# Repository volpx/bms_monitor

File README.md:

# BMS Monitor

Slave BMS module to monitor 24s cells voltages and temperatures.

## Contributors

_Latest first_

- Filippo Volpe

## Features

- 24 cells series
- 32 temperature measurements
- LTC6811-1/-2 both are compatible
- isoSPI cost effective communication interface to the monitor IC directly
- cell balancing
- STM32L0 can be fitted to add logic to the board by itself
- IRda optional communication to the MCU
- compatible, for temperatures, with both NTC and shunt references
- direct SPI connection to the monitor ICs
- usable as two 12S monitor with breakaway slots
- cost reduction in the isolation components if used as 24S monitor
- small footprint, 65mmx115mm

## Configurations

### LTC6811 -1 vs -2

For use with "-1" version the isoSPI link must be daisy chained, hence connecting the master of PORTB to the slave of PORTA of the next IC in the chain. Populate R5 and R6, don't populate R30 R31.

For use with the "-2" version only populate the slave PORTA of each section and connect them in parallel. Then set the address of each section using the solder jumpers. Populate R30 and R31, don't populate R5 R6.

### 24S monitor

Using LTC6811-1 version.

| Component reference         | To fit  | Comment|
|--------------|-----------|------------|
| R11 |   ✔️    |        |
| R12 |   ✔️    |        |
| C18 |   ✔️    |        |
| U12 |   ❌    |        |
| R22 |   ✔️    |        |
| R23 |   ✔️    |        |
| C37 |   ✔️    |        |
| U13 |   ❌    |        |
| FL1 |   ✔️    |        |
| C1 |   ✔️    |        |
| C2 |   ✔️    |        |

### 12S monitor

The board can be splitted along the cutouts to obtain 2 12S monitors of which one has the option to be used with the MCU but both still has full SPI and isoSPI functionality.
In this case using LT6811 -1 or -2 version won't change any functionality.

### Switching PSU

For a more efficient PSU the voltage can be stepped down using a switching regulator.

| Component reference | To fit  | Comment|
|--------------|-----------|------------|
| Q1 |   ❌    |        |

All other PSU components must be populated.

### Low cost PSU

To power the stack monitor a low component count but less efficient psu can be populated using transistor Q1.

| Component reference         | To fit  | Comment|
|--------------|-----------|------------|
| Q1 |   ✔️    |        |
| R14 |   ✔️    |        |
| C19 |   ✔️    |        |
| C21 |   ✔️    |        |
| C27 |   ✔️    |        |
| C29 |   ✔️    |        |

All other PSU components can be left unpopulated.

### SPI vs isoSPI connection

To use the isoSPI connection, connect ISOMD to 1.
To use the direct SPI connection, connect the ISOMD switch to 0 and the ICMP and BIAS resistor can be left unpopulated.

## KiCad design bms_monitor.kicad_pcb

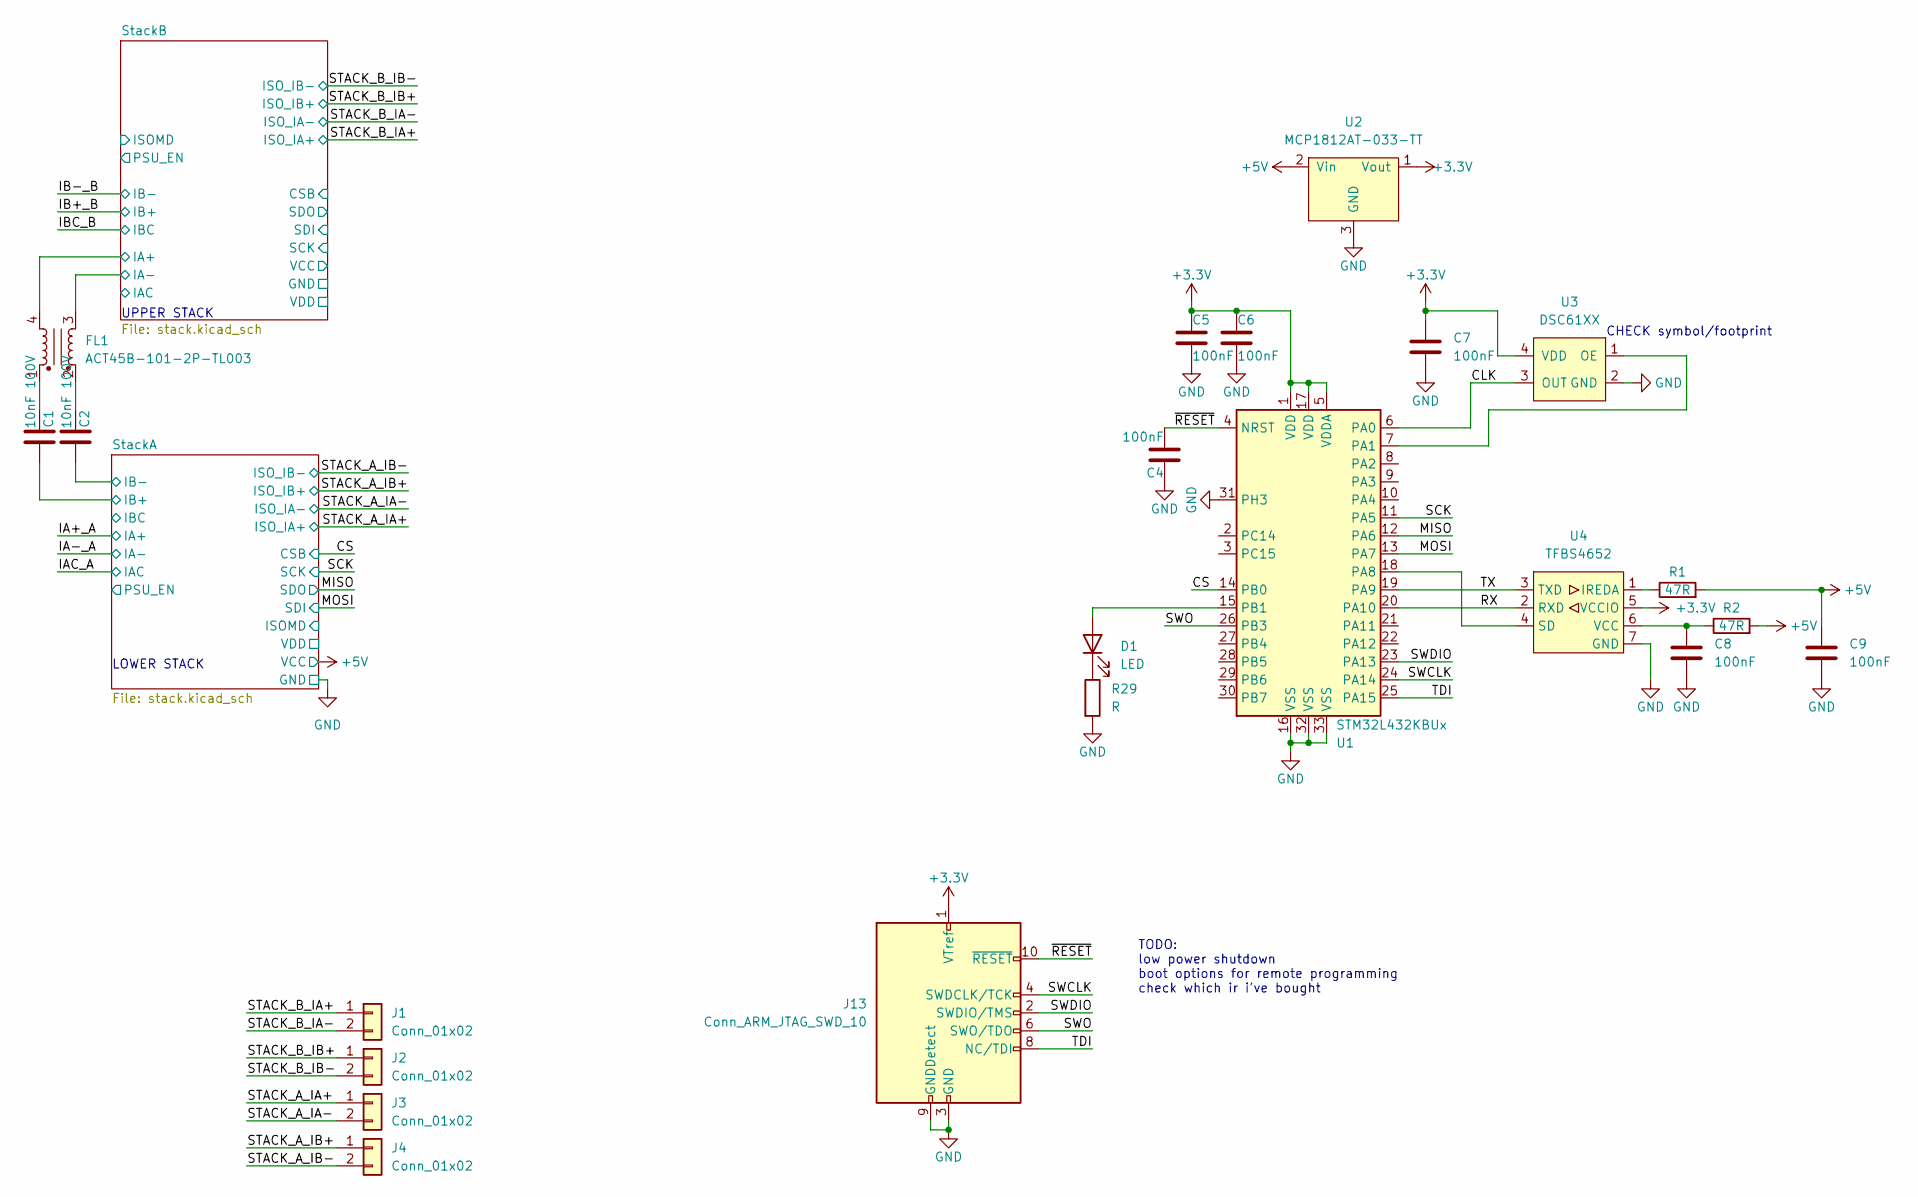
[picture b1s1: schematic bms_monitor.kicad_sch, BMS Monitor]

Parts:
C1, C2: 10nF 100V; C_1206_3216Metric
C4, C5, C6, C7, C8, C9: 100nF; C_0603_1608Metric
D1: LED; LED_0603_1608Metric
FL1: ACT45B-101-2P-TL003; ACT45B-xxx-2P-TL003
J1, J2, J3, J4: Conn_01x02; Molex_Micro-Fit_3.0_43650-0215_1x02_P3.00mm_Vertical
J13: Conn_ARM_JTAG_SWD_10; PinHeader_2x05_P1.27mm_Vertical_SMD
R1, R2: 47R; R_0603_1608Metric
R29: R; R_0603_1608Metric
U1: STM32L432KBUx; QFN-32-1EP_5x5mm_P0.5mm_EP3.45x3.45mm
U2: MCP1812AT-033-TT; SOT-23
U3: DSC61XX; VLGA-4_2x2.5mm_P1.65mm
U4: TFBS4652

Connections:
+3.3V: C5.1, C6.1, C7.1, J13.1 (VTref), U1.1 (VDD), U1.5 (VDDA), U1.17 (VDD), U2.1 (Vout), U3.4 (VDD), U4.5 (VCCIO); also elsewhere on the board
+5V: C9.1, R1.2, R2.2, U2.2 (Vin); also elsewhere on the board
/CLK: U1.6 (PA0), U3.3 (OUT)
/CS: U1.14 (PB0); also elsewhere on the board
/IA+_A: U1.11 (PA5); also elsewhere on the board
/MISO: U1.12 (PA6); also elsewhere on the board
/MOSI: U1.13 (PA7); also elsewhere on the board
/RX: U1.20 (PA10), U4.2 (RXD)
/STACK_A_IA+: J3.1; also elsewhere on the board
/STACK_A_IA-: J3.2; also elsewhere on the board
/STACK_A_IB+: J4.1; also elsewhere on the board
/STACK_A_IB-: J4.2; also elsewhere on the board
/STACK_B_IA+: J1.1; also elsewhere on the board
/STACK_B_IA-: J1.2; also elsewhere on the board
/STACK_B_IB+: J2.1; also elsewhere on the board
/STACK_B_IB-: J2.2; also elsewhere on the board
/SWCLK: J13.4 (SWDCLK/TCK), U1.24 (PA14)
/SWDIO: J13.2 (SWDIO/TMS), U1.23 (PA13)
/SWO: J13.6 (SWO/TDO), U1.26 (PB3)
/StackA/A2: C2.1; also elsewhere on the board
/StackA/A3: C1.1; also elsewhere on the board
/StackB/CSB: FL1.3; also elsewhere on the board
/StackB/IA+: FL1.4; also elsewhere on the board
/TDI: J13.8 (NC/TDI), U1.25 (PA15)
/TX: U1.19 (PA9), U4.3 (TXD)
/~RESET: C4.2, J13.10 (~RESET), U1.4 (NRST)
GND: C4.1, C5.2, C6.2, C7.2, C8.2, C9.2, J13.3 (GND), J13.5 (GND), J13.9 (GNDDetect), R29.2, U1.16 (VSS), U1.31 (PH3), U1.32 (VSS), U1.33 (VSS), U2.3 (GND), U3.2 (GND), U4.7 (GND); also elsewhere on the board
unnamed: C1.2, FL1.1
unnamed: C2.2, FL1.2
unnamed: D1.2 (A), U1.15 (PB1)
unnamed: D1.1 (K), R29.1
unnamed: U1.7 (PA1), U3.1 (OE)
unnamed: U1.18 (PA8), U4.4 (SD)
unnamed: R1.1, U4.1 (IREDA)
unnamed: C8.1, R2.1, U4.6 (VCC)

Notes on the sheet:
UPPER STACK
LOWER STACK
CHECK symbol/footprint
TODO: low power shutdown boot options for remote programming check which ir i've bought

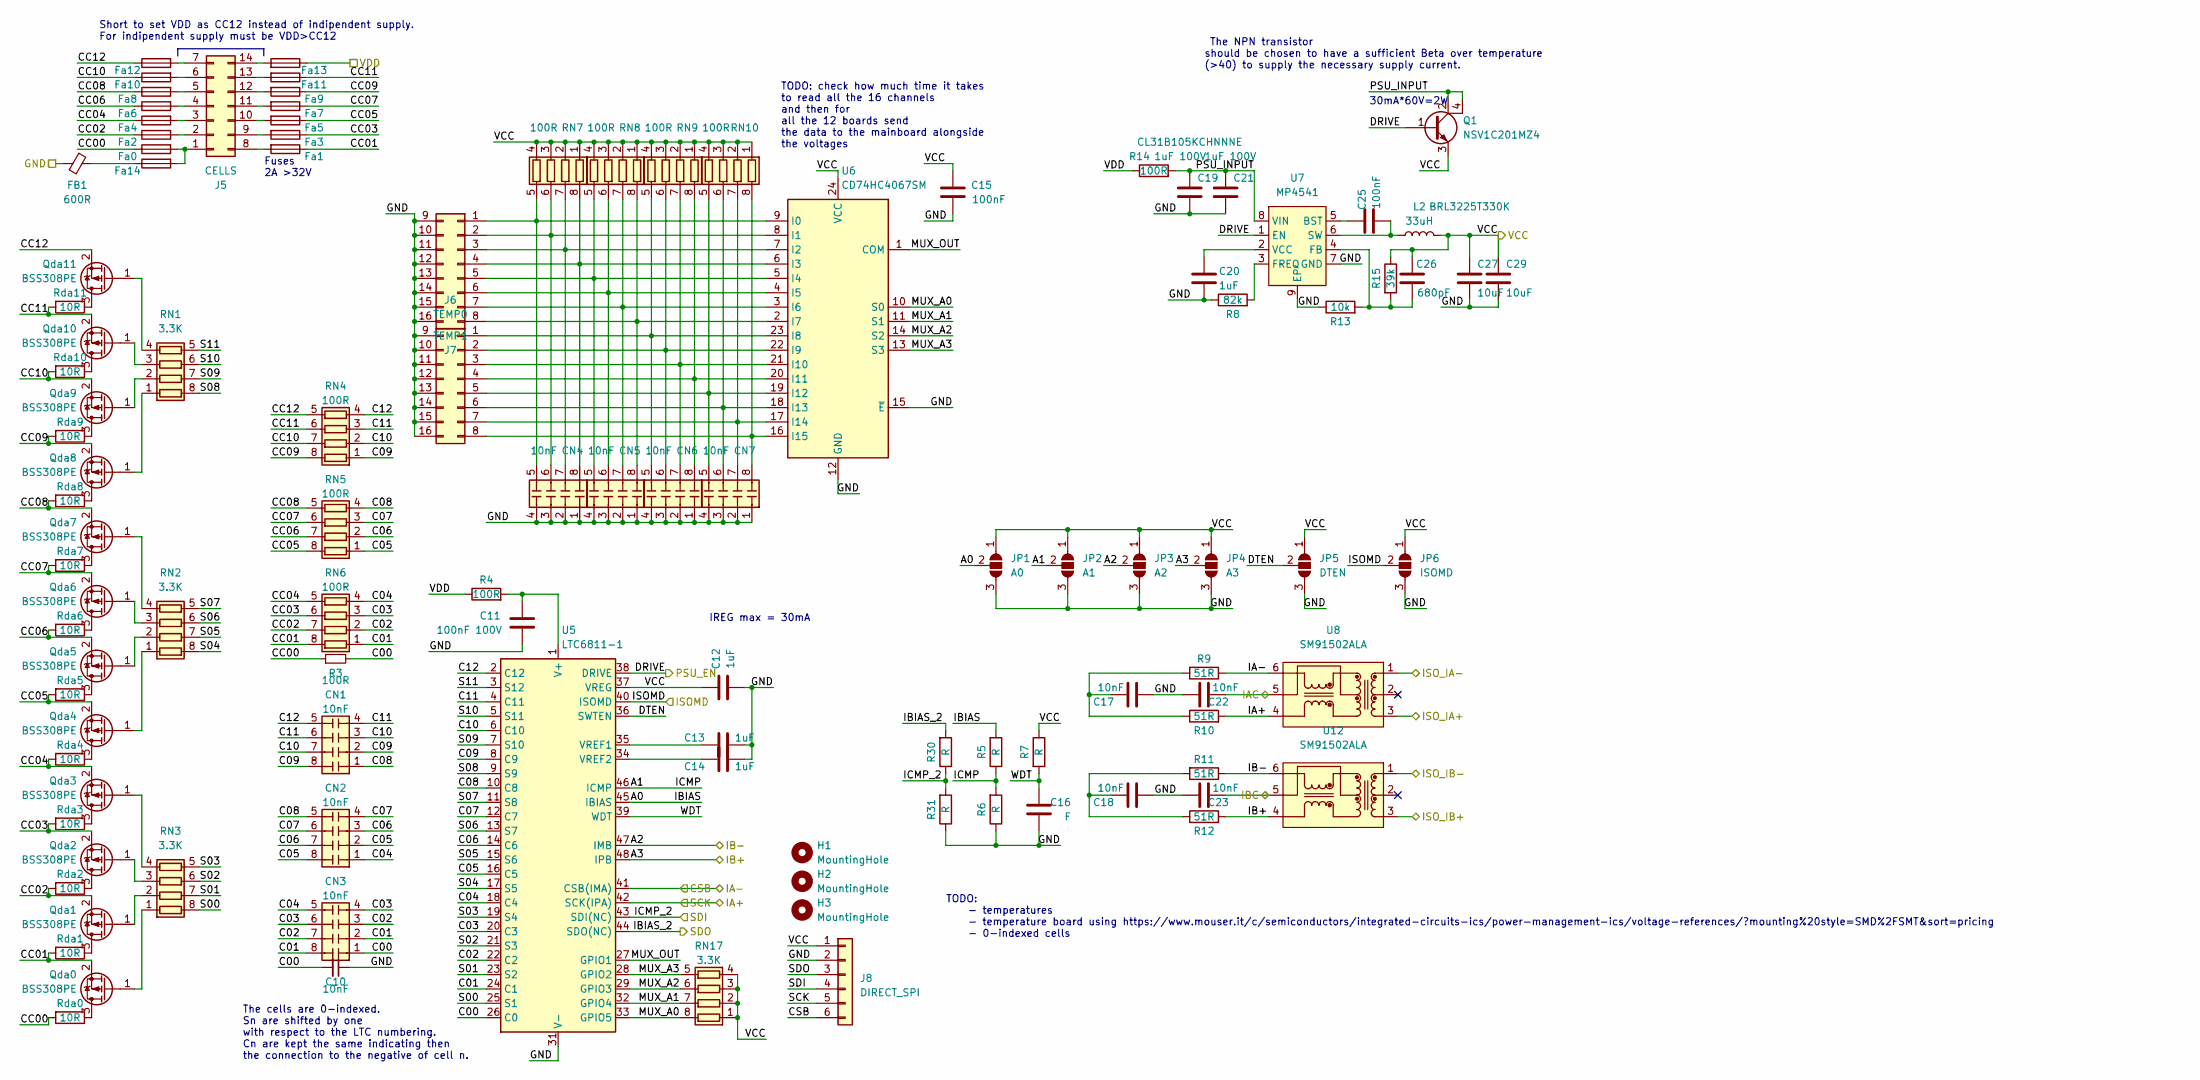
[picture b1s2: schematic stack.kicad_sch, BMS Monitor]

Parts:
C10, C17, C18, C22, C23: 10nF; C_0603_1608Metric
C11: 100nF 100V; C_1210_3225Metric
C12, C13, C14, C20: 1uF; C_0805_2012Metric
C15, C25: 100nF; C_0603_1608Metric
C16: F; C_0603_1608Metric
C19, C21: 1uF 100V; C_1210_3225Metric; Partname CL31B105KCHNNNE
C26: 680pF; C_0603_1608Metric
C27, C29: 10uF; C_0805_2012Metric
CN1, CN2, CN3, CN4, CN5, CN6, CN7: 10nF; R_Array_Convex_4x0603; Partname W3A45C103MAT2A
FB1: 600R; R_0805_2012Metric
Fa0, Fa1, Fa2, Fa3, Fa4, Fa5, Fa6, Fa7, Fa8, Fa9, Fa10, Fa11, Fa12, Fa13, Fa14: 2A; Fuse_0805_2012Metric
H1, H2, H3: MountingHole; MountingHole_3.2mm_M3_ISO14580
J5: CELLS; Molex_Nano-Fit_105314-xx14_2x07_P2.50mm_Horizontal
J6: TEMP0; Molex_Nano-Fit_105314-xx16_2x08_P2.50mm_Horizontal
J7: TEMP1; Molex_Nano-Fit_105314-xx16_2x08_P2.50mm_Horizontal
J8: DIRECT_SPI; Molex_Nano-Fit_105309-xx06_1x06_P2.50mm_Vertical
JP1: A0; SolderJumper-3_P1.3mm_Open_RoundedPad1.0x1.5mm
JP2: A1; SolderJumper-3_P1.3mm_Open_RoundedPad1.0x1.5mm
JP3: A2; SolderJumper-3_P1.3mm_Open_RoundedPad1.0x1.5mm
JP4: A3; SolderJumper-3_P1.3mm_Open_RoundedPad1.0x1.5mm
JP5: DTEN; SolderJumper-3_P1.3mm_Open_RoundedPad1.0x1.5mm
JP6: ISOMD; SolderJumper-3_P1.3mm_Open_RoundedPad1.0x1.5mm
L2: 33uH; L_1210_3225Metric; Partname BRL3225T330K
Q1: NSV1C201MZ4; SOT-223
Qda0, Qda1, Qda2, Qda3, Qda4, Qda5, Qda6, Qda7, Qda8, Qda9, Qda10, Qda11: BSS308PE; TSOT-23
R3: 100R; R_0603_1608Metric
R4, R14: 100R; R_0805_2012Metric
R5, R6, R7, R30, R31: R; R_0603_1608Metric
R8: 82k; R_0603_1608Metric
R9, R10, R11, R12: 51R; R_0603_1608Metric
R13: 10k; R_0603_1608Metric
R15: 39k; R_0603_1608Metric
RN1, RN2, RN3, RN17: 3.3K; R_Array_Convex_4x0603
RN4, RN5, RN6, RN7, RN8, RN9, RN10: 100R; R_Array_Convex_4x0603
Rda0, Rda1, Rda2, Rda3, Rda4, Rda5, Rda6, Rda7, Rda8, Rda9, Rda10, Rda11: 10R; R_2512_6332Metric
U5: LTC6811-1; SSOP-48_5.3x12.8mm_P0.5mm
U6: CD74HC4067SM; SSOP-24_5.3x8.2mm_P0.65mm
U7: MP4541; SOIC-8-1EP_3.9x4.9mm_P1.27mm_EP2.514x3.2mm
U8, U12: SM91502ALA

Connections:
+5V: C12.2, C15.2, C26.1, C27.1, C29.1, J8.1, JP1.1 (A), JP2.1 (A), JP3.1 (A), JP4.1 (A), JP5.1 (A), JP6.1 (A), L2.2, Q1.3 (E), R7.1, R15.1, RN7.1 (R1.1), RN7.2 (R2.1), RN7.3 (R3.1), RN7.4 (R4.1), RN8.1 (R1.1), RN8.2 (R2.1), RN8.3 (R3.1), RN8.4 (R4.1), RN9.1 (R1.1), RN9.2 (R2.1), RN9.3 (R3.1), RN9.4 (R4.1), RN10.1 (R1.1), RN10.2 (R2.1), RN10.3 (R3.1), RN10.4 (R4.1), RN17.1 (R1.1), RN17.2 (R2.1), RN17.3 (R3.1), RN17.4 (R4.1), U5.37 (VREG), U6.24 (VCC); also elsewhere on the board
/CS: J8.6, R9.1, U5.41 (CSB(IMA)), U8.6; also elsewhere on the board
/IA+_A: J8.5, R10.2, U5.42 (SCK(IPA)), U8.4; also elsewhere on the board
/IAC_A: C22.2, U8.5
/MISO: J8.3, R30.2, U5.44 (SDO(NC)); also elsewhere on the board
/MOSI: J8.4, R30.1, R31.2, U5.43 (SDI(NC)); also elsewhere on the board
/STACK_A_IA+: U8.3; also elsewhere on the board
/STACK_A_IA-: U8.1; also elsewhere on the board
/STACK_A_IB+: U12.3; also elsewhere on the board
/STACK_A_IB-: U12.1; also elsewhere on the board
/StackA/A0: JP1.2 (C), R5.2, U5.45 (IBIAS)
/StackA/A1: JP2.2 (C), R5.1, R6.2, U5.46 (ICMP)
/StackA/A2: JP3.2 (C), R11.1, U5.47 (IMB), U12.6; also elsewhere on the board
/StackA/A3: JP4.2 (C), R12.2, U5.48 (IPB), U12.4; also elsewhere on the board
/StackA/C00: C10.2, CN3.1 (R1.1), R3.2, U5.26 (C0)
/StackA/C01: CN3.2 (R2.1), CN3.8 (R1.2), RN6.1 (R1.1), U5.24 (C1)
/StackA/C02: CN3.3 (R3.1), CN3.7 (R2.2), RN6.2 (R2.1), U5.22 (C2)
/StackA/C03: CN3.4 (R4.1), CN3.6 (R3.2), RN6.3 (R3.1), U5.20 (C3)
/StackA/C04: CN2.1 (R1.1), CN3.5 (R4.2), RN6.4 (R4.1), U5.18 (C4)
/StackA/C05: CN2.2 (R2.1), CN2.8 (R1.2), RN5.1 (R1.1), U5.16 (C5)
/StackA/C06: CN2.3 (R3.1), CN2.7 (R2.2), RN5.2 (R2.1), U5.14 (C6)
/StackA/C07: CN2.4 (R4.1), CN2.6 (R3.2), RN5.3 (R3.1), U5.12 (C7)
/StackA/C08: CN1.1 (R1.1), CN2.5 (R4.2), RN5.4 (R4.1), U5.10 (C8)
/StackA/C09: CN1.2 (R2.1), CN1.8 (R1.2), RN4.1 (R1.1), U5.8 (C9)
/StackA/C10: CN1.3 (R3.1), CN1.7 (R2.2), RN4.2 (R2.1), U5.6 (C10)
/StackA/C11: CN1.4 (R4.1), CN1.6 (R3.2), RN4.3 (R3.1), U5.4 (C11)
/StackA/C12: CN1.5 (R4.2), RN4.4 (R4.1), U5.2 (C12)
/StackA/CC00: Fa0.1, R3.1, Rda0.2
/StackA/CC01: Fa1.1, Qda0.2 (S), RN6.8 (R1.2), Rda1.2
/StackA/CC02: Fa2.1, Qda1.2 (S), RN6.7 (R2.2), Rda2.2
/StackA/CC03: Fa3.1, Qda2.2 (S), RN6.6 (R3.2), Rda3.2
/StackA/CC04: Fa4.1, Qda3.2 (S), RN6.5 (R4.2), Rda4.2
/StackA/CC05: Fa5.1, Qda4.2 (S), RN5.8 (R1.2), Rda5.2
/StackA/CC06: Fa6.1, Qda5.2 (S), RN5.7 (R2.2), Rda6.2
/StackA/CC07: Fa7.1, Qda6.2 (S), RN5.6 (R3.2), Rda7.2
/StackA/CC08: Fa8.1, Qda7.2 (S), RN5.5 (R4.2), Rda8.2
/StackA/CC09: Fa9.1, Qda8.2 (S), RN4.8 (R1.2), Rda9.2
/StackA/CC10: Fa10.1, Qda9.2 (S), RN4.7 (R2.2), Rda10.2
/StackA/CC11: Fa11.1, Qda10.2 (S), RN4.6 (R3.2), Rda11.2
/StackA/CC12: Fa12.1, Qda11.2 (S), RN4.5 (R4.2)
/StackA/DRIVE: Q1.1 (B), U5.38 (DRIVE), U7.1 (EN)
/StackA/DTEN: JP5.2 (C), U5.36 (SWTEN)
/StackA/IBC: C23.2, U12.5
/StackA/ISOMD: JP6.2 (C), U5.40 (ISOMD)
/StackA/MUX_A0: RN17.8 (R1.2), U5.33 (GPIO5), U6.10 (S0)
/StackA/MUX_A1: RN17.7 (R2.2), U5.32 (GPIO4), U6.11 (S1)
/StackA/MUX_A2: RN17.6 (R3.2), U5.29 (GPIO3), U6.14 (S2)
/StackA/MUX_A3: RN17.5 (R4.2), U5.28 (GPIO2), U6.13 (S3)
/StackA/MUX_OUT: U5.27 (GPIO1), U6.1 (COM)
/StackA/PSU_INPUT: C19.1, C21.1, Q1.2 (C), Q1.4 (C), R14.2, U7.8 (VIN)
/StackA/S00: RN3.8 (R1.2), U5.25 (S1)
/StackA/S01: RN3.7 (R2.2), U5.23 (S2)
/StackA/S02: RN3.6 (R3.2), U5.21 (S3)
/StackA/S03: RN3.5 (R4.2), U5.19 (S4)
/StackA/S04: RN2.8 (R1.2), U5.17 (S5)
/StackA/S05: RN2.7 (R2.2), U5.15 (S6)
/StackA/S06: RN2.6 (R3.2), U5.13 (S7)
/StackA/S07: RN2.5 (R4.2), U5.11 (S8)
/StackA/S08: RN1.8 (R1.2), U5.9 (S9)
/StackA/S09: RN1.7 (R2.2), U5.7 (S10)
/StackA/S10: RN1.6 (R3.2), U5.5 (S11)
/StackA/S11: RN1.5 (R4.2), U5.3 (S12)
/StackA/VDD: Fa13.1, R4.1, R14.1
/StackA/WDT: C16.1, R7.2, U5.39 (WDT)
GND: C10.1, C11.2, C12.1, C13.1, C14.1, C15.1, C16.2, C17.2, C18.2, C19.2, C20.2, C21.2, C22.1, C23.1, C27.2, C29.2, CN4.1 (R1.1), CN4.2 (R2.1), CN4.3 (R3.1), CN4.4 (R4.1), CN5.1 (R1.1), CN5.2 (R2.1), CN5.3 (R3.1), CN5.4 (R4.1), CN6.1 (R1.1), CN6.2 (R2.1), CN6.3 (R3.1), CN6.4 (R4.1), CN7.1 (R1.1), CN7.2 (R2.1), CN7.3 (R3.1), CN7.4 (R4.1), FB1.2, J6.9, J6.10, J6.11, J6.12, J6.13, J6.14, J6.15, J6.16, J7.9, J7.10, J7.11, J7.12, J7.13, J7.14, J7.15, J7.16, J8.2, JP1.3 (B), JP2.3 (B), JP3.3 (B), JP4.3 (B), JP5.3 (B), JP6.3 (B), R6.1, R8.1, R13.1, R31.1, U5.30 (V-), U5.31 (V-), U6.12 (GND), U6.15 (~E), U7.7 (GND), U7.9 (EP); also elsewhere on the board
unnamed: C17.1, R9.2, R10.1
unnamed: C18.1, R11.2, R12.1
unnamed: CN4.8 (R1.2), J7.4, RN7.8 (R1.2), U6.6 (I3)
unnamed: CN4.7 (R2.2), J7.3, RN7.7 (R2.2), U6.7 (I2)
unnamed: CN4.6 (R3.2), J7.2, RN7.6 (R3.2), U6.8 (I1)
unnamed: CN4.5 (R4.2), J7.1, RN7.5 (R4.2), U6.9 (I0)
unnamed: CN5.8 (R1.2), J7.8, RN8.8 (R1.2), U6.2 (I7)
unnamed: CN5.7 (R2.2), J7.7, RN8.7 (R2.2), U6.3 (I6)
unnamed: CN5.6 (R3.2), J7.6, RN8.6 (R3.2), U6.4 (I5)
unnamed: CN5.5 (R4.2), J7.5, RN8.5 (R4.2), U6.5 (I4)
unnamed: CN6.8 (R1.2), J6.4, RN9.8 (R1.2), U6.20 (I11)
unnamed: CN6.7 (R2.2), J6.3, RN9.7 (R2.2), U6.21 (I10)
unnamed: CN6.6 (R3.2), J6.2, RN9.6 (R3.2), U6.22 (I9)
unnamed: CN6.5 (R4.2), J6.1, RN9.5 (R4.2), U6.23 (I8)
unnamed: CN7.8 (R1.2), J6.8, RN10.8 (R1.2), U6.16 (I15)
unnamed: CN7.7 (R2.2), J6.7, RN10.7 (R2.2), U6.17 (I14)
unnamed: CN7.6 (R3.2), J6.6, RN10.6 (R3.2), U6.18 (I13)
unnamed: CN7.5 (R4.2), J6.5, RN10.5 (R4.2), U6.19 (I12)
unnamed: FB1.1, Fa14.1
unnamed: Fa0.2, Fa14.2, J5.1
unnamed: Fa2.2, J5.2
unnamed: Fa4.2, J5.3
unnamed: Fa6.2, J5.4
unnamed: Fa8.2, J5.5
unnamed: Fa10.2, J5.6
unnamed: Fa12.2, J5.7
unnamed: Fa1.2, J5.8
unnamed: Fa3.2, J5.9
unnamed: Fa5.2, J5.10
unnamed: Fa7.2, J5.11
unnamed: Fa9.2, J5.12
unnamed: Fa11.2, J5.13
unnamed: Fa13.2, J5.14
unnamed: Qda0.3 (D), Rda0.1
unnamed: Qda0.1 (G), RN3.1 (R1.1)
unnamed: Qda1.3 (D), Rda1.1
unnamed: Qda1.1 (G), RN3.2 (R2.1)
unnamed: Qda2.3 (D), Rda2.1
unnamed: Qda2.1 (G), RN3.3 (R3.1)
unnamed: Qda3.3 (D), Rda3.1
unnamed: Qda3.1 (G), RN3.4 (R4.1)
unnamed: Qda4.3 (D), Rda4.1
unnamed: Qda4.1 (G), RN2.1 (R1.1)
unnamed: Qda5.3 (D), Rda5.1
unnamed: Qda5.1 (G), RN2.2 (R2.1)
unnamed: Qda6.3 (D), Rda6.1
unnamed: Qda6.1 (G), RN2.3 (R3.1)
unnamed: Qda7.3 (D), Rda7.1
unnamed: Qda7.1 (G), RN2.4 (R4.1)
unnamed: Qda8.3 (D), Rda8.1
unnamed: Qda8.1 (G), RN1.1 (R1.1)
unnamed: Qda9.3 (D), Rda9.1
unnamed: Qda9.1 (G), RN1.2 (R2.1)
unnamed: Qda10.3 (D), Rda10.1
unnamed: Qda10.1 (G), RN1.3 (R3.1)
unnamed: Qda11.3 (D), Rda11.1
unnamed: Qda11.1 (G), RN1.4 (R4.1)
unnamed: C11.1, R4.2, U5.1 (V+)
unnamed: C13.2, U5.35 (VREF1)
unnamed: C14.2, U5.34 (VREF2)
unnamed: C25.1, U7.5 (BST)
unnamed: C26.2, R13.2, R15.2, U7.4 (FB)
unnamed: R8.2, U7.3 (FREQ)
unnamed: C25.2, L2.1, U7.6 (SW)
unnamed: C20.1, U7.2 (VCC)

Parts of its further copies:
C30, C37, C38, C42, C43: 10nF; C_0603_1608Metric
C31: 100nF 100V; C_1210_3225Metric
C32, C33, C34, C40: 1uF; C_0805_2012Metric
C35, C45: 100nF; C_0603_1608Metric
C36: F; C_0603_1608Metric
C39, C41: 1uF 100V; C_1210_3225Metric; Partname CL31B105KCHNNNE
C46: 680pF; C_0603_1608Metric
C47, C49: 10uF; C_0805_2012Metric
CN8, CN9, CN10, CN11, CN12, CN13, CN14: 10nF; R_Array_Convex_4x0603; Partname W3A45C103MAT2A
F13, F14, F15, F16, F17, F18, F19, F20, F21, F22, F23, F24, F25: 2A; Fuse_0805_2012Metric
FB2: 600R; R_0805_2012Metric
Fb3, Fb14: 2A; Fuse_0805_2012Metric
H4, H5, H6: MountingHole; MountingHole_3.2mm_M3_ISO14580
J9: CELLS; Molex_Nano-Fit_105314-xx14_2x07_P2.50mm_Horizontal
J10: TEMP0; Molex_Nano-Fit_105314-xx16_2x08_P2.50mm_Horizontal
J11: TEMP1; Molex_Nano-Fit_105314-xx16_2x08_P2.50mm_Horizontal
J12: DIRECT_SPI; Molex_Nano-Fit_105309-xx06_1x06_P2.50mm_Vertical
JP7: A0; SolderJumper-3_P1.3mm_Open_RoundedPad1.0x1.5mm
JP8: A1; SolderJumper-3_P1.3mm_Open_RoundedPad1.0x1.5mm
JP9: A2; SolderJumper-3_P1.3mm_Open_RoundedPad1.0x1.5mm
JP10: A3; SolderJumper-3_P1.3mm_Open_RoundedPad1.0x1.5mm
JP11: DTEN; SolderJumper-3_P1.3mm_Open_RoundedPad1.0x1.5mm
JP12: ISOMD; SolderJumper-3_P1.3mm_Open_RoundedPad1.0x1.5mm
L3: 33uH; L_1210_3225Metric; Partname BRL3225T330K
Q2: NSV1C201MZ4; SOT-223
Qdb0, Qdb1, Qdb2, Qdb3, Qdb4, Qdb5, Qdb6, Qdb7, Qdb8, Qdb9, Qdb10, Qdb11: BSS308PE; TSOT-23
R16: 100R; R_0603_1608Metric
R17, R27: 100R; R_0805_2012Metric
R18, R19, R20, R32, R33: R; R_0603_1608Metric
R21: 82k; R_0603_1608Metric
R22, R23, R24, R25: 51R; R_0603_1608Metric
R26: 10k; R_0603_1608Metric
R28: 39k; R_0603_1608Metric
RN11, RN12, RN13, RN22: 3.3K; R_Array_Convex_4x0603
RN14, RN15, RN16, RN18, RN19, RN20, RN21: 100R; R_Array_Convex_4x0603
Rdb0, Rdb1, Rdb2, Rdb3, Rdb4, Rdb5, Rdb6, Rdb7, Rdb8, Rdb9, Rdb10, Rdb11: 10R; R_2512_6332Metric
U9: LTC6811-1; SSOP-48_5.3x12.8mm_P0.5mm
U10: CD74HC4067SM; SSOP-24_5.3x8.2mm_P0.65mm
U11: MP4541; SOIC-8-1EP_3.9x4.9mm_P1.27mm_EP2.514x3.2mm
U13, U14: SM91502ALA

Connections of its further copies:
/IB+_B: JP10.2 (C), R25.2, U9.48 (IPB), U14.4
/IB-_B: JP9.2 (C), R24.1, U9.47 (IMB), U14.6
/IBC_B: C43.2, U14.5
/STACK_B_IA+: U13.3; also elsewhere on the board
/STACK_B_IA-: U13.1; also elsewhere on the board
/STACK_B_IB+: U14.3; also elsewhere on the board
/STACK_B_IB-: U14.1; also elsewhere on the board
/StackB/A0: JP7.2 (C), R18.2, U9.45 (IBIAS)
/StackB/A1: JP8.2 (C), R18.1, R19.2, U9.46 (ICMP)
/StackB/C00: C30.2, CN14.1 (R1.1), R16.2, U9.26 (C0)
/StackB/C01: CN14.2 (R2.1), CN14.8 (R1.2), RN16.1 (R1.1), U9.24 (C1)
/StackB/C02: CN14.3 (R3.1), CN14.7 (R2.2), RN16.2 (R2.1), U9.22 (C2)
/StackB/C03: CN14.4 (R4.1), CN14.6 (R3.2), RN16.3 (R3.1), U9.20 (C3)
/StackB/C04: CN9.1 (R1.1), CN14.5 (R4.2), RN16.4 (R4.1), U9.18 (C4)
/StackB/C05: CN9.2 (R2.1), CN9.8 (R1.2), RN15.1 (R1.1), U9.16 (C5)
/StackB/C06: CN9.3 (R3.1), CN9.7 (R2.2), RN15.2 (R2.1), U9.14 (C6)
/StackB/C07: CN9.4 (R4.1), CN9.6 (R3.2), RN15.3 (R3.1), U9.12 (C7)
/StackB/C08: CN8.1 (R1.1), CN9.5 (R4.2), RN15.4 (R4.1), U9.10 (C8)
/StackB/C09: CN8.2 (R2.1), CN8.8 (R1.2), RN14.1 (R1.1), U9.8 (C9)
/StackB/C10: CN8.3 (R3.1), CN8.7 (R2.2), RN14.2 (R2.1), U9.6 (C10)
/StackB/C11: CN8.4 (R4.1), CN8.6 (R3.2), RN14.3 (R3.1), U9.4 (C11)
/StackB/C12: CN8.5 (R4.2), RN14.4 (R4.1), U9.2 (C12)
/StackB/CC00: F19.1, R16.1, Rdb0.2
/StackB/CC01: F25.1, Qdb0.2 (S), RN16.8 (R1.2), Rdb1.2
/StackB/CC02: F18.1, Qdb1.2 (S), RN16.7 (R2.2), Rdb2.2
/StackB/CC03: F24.1, Qdb2.2 (S), RN16.6 (R3.2), Rdb3.2
/StackB/CC04: F17.1, Qdb3.2 (S), RN16.5 (R4.2), Rdb4.2
/StackB/CC05: F23.1, Qdb4.2 (S), RN15.8 (R1.2), Rdb5.2
/StackB/CC06: F16.1, Qdb5.2 (S), RN15.7 (R2.2), Rdb6.2
/StackB/CC07: F22.1, Qdb6.2 (S), RN15.6 (R3.2), Rdb7.2
/StackB/CC08: F15.1, Qdb7.2 (S), RN15.5 (R4.2), Rdb8.2
/StackB/CC09: F21.1, Qdb8.2 (S), RN14.8 (R1.2), Rdb9.2
/StackB/CC10: F14.1, Qdb9.2 (S), RN14.7 (R2.2), Rdb10.2
/StackB/CC11: F20.1, Qdb10.2 (S), RN14.6 (R3.2), Rdb11.2
/StackB/CC12: F13.1, Qdb11.2 (S), RN14.5 (R4.2)
/StackB/CSB: J12.6, R22.1, U9.41 (CSB(IMA)), U13.6; also elsewhere on the board
/StackB/DRIVE: Q2.1 (B), U9.38 (DRIVE), U11.1 (EN)
/StackB/DTEN: JP11.2 (C), U9.36 (SWTEN)
/StackB/GND: C30.1, C31.2, C32.1, C33.1, C34.1, C35.1, C36.2, C37.2, C38.2, C39.2, C40.2, C41.2, C42.1, C43.1, C47.2, C49.2, CN10.1 (R1.1), CN10.2 (R2.1), CN10.3 (R3.1), CN10.4 (R4.1), CN11.1 (R1.1), CN11.2 (R2.1), CN11.3 (R3.1), CN11.4 (R4.1), CN12.1 (R1.1), CN12.2 (R2.1), CN12.3 (R3.1), CN12.4 (R4.1), CN13.1 (R1.1), CN13.2 (R2.1), CN13.3 (R3.1), CN13.4 (R4.1), FB2.2, J10.9, J10.10, J10.11, J10.12, J10.13, J10.14, J10.15, J10.16, J11.9, J11.10, J11.11, J11.12, J11.13, J11.14, J11.15, J11.16, J12.2, JP7.3 (B), JP8.3 (B), JP9.3 (B), JP10.3 (B), JP11.3 (B), JP12.3 (B), R19.1, R21.1, R26.1, R33.1, U9.30 (V-), U9.31 (V-), U10.12 (GND), U10.15 (~E), U11.7 (GND), U11.9 (EP)
/StackB/IA+: J12.5, R23.2, U9.42 (SCK(IPA)), U13.4; also elsewhere on the board
/StackB/IAC: C42.2, U13.5
/StackB/IBIAS_2: J12.3, R32.2, U9.44 (SDO(NC))
/StackB/ICMP_2: J12.4, R32.1, R33.2, U9.43 (SDI(NC))
/StackB/ISOMD: JP12.2 (C), U9.40 (ISOMD)
/StackB/MUX_A0: RN22.8 (R1.2), U9.33 (GPIO5), U10.10 (S0)
/StackB/MUX_A1: RN22.7 (R2.2), U9.32 (GPIO4), U10.11 (S1)
/StackB/MUX_A2: RN22.6 (R3.2), U9.29 (GPIO3), U10.14 (S2)
/StackB/MUX_A3: RN22.5 (R4.2), U9.28 (GPIO2), U10.13 (S3)
/StackB/MUX_OUT: U9.27 (GPIO1), U10.1 (COM)
/StackB/PSU_INPUT: C39.1, C41.1, Q2.2 (C), Q2.4 (C), R27.2, U11.8 (VIN)
/StackB/S00: RN13.8 (R1.2), U9.25 (S1)
/StackB/S01: RN13.7 (R2.2), U9.23 (S2)
/StackB/S02: RN13.6 (R3.2), U9.21 (S3)
/StackB/S03: RN13.5 (R4.2), U9.19 (S4)
/StackB/S04: RN12.8 (R1.2), U9.17 (S5)
/StackB/S05: RN12.7 (R2.2), U9.15 (S6)
/StackB/S06: RN12.6 (R3.2), U9.13 (S7)
/StackB/S07: RN12.5 (R4.2), U9.11 (S8)
/StackB/S08: RN11.8 (R1.2), U9.9 (S9)
/StackB/S09: RN11.7 (R2.2), U9.7 (S10)
/StackB/S10: RN11.6 (R3.2), U9.5 (S11)
/StackB/S11: RN11.5 (R4.2), U9.3 (S12)
/StackB/VCC: C32.2, C35.2, C46.1, C47.1, C49.1, J12.1, JP7.1 (A), JP8.1 (A), JP9.1 (A), JP10.1 (A), JP11.1 (A), JP12.1 (A), L3.2, Q2.3 (E), R20.1, R28.1, RN18.1 (R1.1), RN18.2 (R2.1), RN18.3 (R3.1), RN18.4 (R4.1), RN19.1 (R1.1), RN19.2 (R2.1), RN19.3 (R3.1), RN19.4 (R4.1), RN20.1 (R1.1), RN20.2 (R2.1), RN20.3 (R3.1), RN20.4 (R4.1), RN21.1 (R1.1), RN21.2 (R2.1), RN21.3 (R3.1), RN21.4 (R4.1), RN22.1 (R1.1), RN22.2 (R2.1), RN22.3 (R3.1), RN22.4 (R4.1), U9.37 (VREG), U10.24 (VCC)
/StackB/VDD: Fb3.1, R17.1, R27.1
/StackB/WDT: C36.1, R20.2, U9.39 (WDT)
unnamed: C37.1, R22.2, R23.1
unnamed: C38.1, R24.2, R25.1
unnamed: CN10.8 (R1.2), J11.4, RN18.8 (R1.2), U10.6 (I3)
unnamed: CN10.7 (R2.2), J11.3, RN18.7 (R2.2), U10.7 (I2)
unnamed: CN10.6 (R3.2), J11.2, RN18.6 (R3.2), U10.8 (I1)
unnamed: CN10.5 (R4.2), J11.1, RN18.5 (R4.2), U10.9 (I0)
unnamed: CN11.8 (R1.2), J11.8, RN19.8 (R1.2), U10.2 (I7)
unnamed: CN11.7 (R2.2), J11.7, RN19.7 (R2.2), U10.3 (I6)
unnamed: CN11.6 (R3.2), J11.6, RN19.6 (R3.2), U10.4 (I5)
unnamed: CN11.5 (R4.2), J11.5, RN19.5 (R4.2), U10.5 (I4)
unnamed: CN12.8 (R1.2), J10.4, RN20.8 (R1.2), U10.20 (I11)
unnamed: CN12.7 (R2.2), J10.3, RN20.7 (R2.2), U10.21 (I10)
unnamed: CN12.6 (R3.2), J10.2, RN20.6 (R3.2), U10.22 (I9)
unnamed: CN12.5 (R4.2), J10.1, RN20.5 (R4.2), U10.23 (I8)
unnamed: CN13.8 (R1.2), J10.8, RN21.8 (R1.2), U10.16 (I15)
unnamed: CN13.7 (R2.2), J10.7, RN21.7 (R2.2), U10.17 (I14)
unnamed: CN13.6 (R3.2), J10.6, RN21.6 (R3.2), U10.18 (I13)
unnamed: CN13.5 (R4.2), J10.5, RN21.5 (R4.2), U10.19 (I12)
unnamed: FB2.1, Fb14.1
unnamed: F19.2, Fb14.2, J9.1
unnamed: F18.2, J9.2
unnamed: F17.2, J9.3
unnamed: F16.2, J9.4
unnamed: F15.2, J9.5
unnamed: F14.2, J9.6
unnamed: F13.2, J9.7
unnamed: F25.2, J9.8
unnamed: F24.2, J9.9
unnamed: F23.2, J9.10
unnamed: F22.2, J9.11
unnamed: F21.2, J9.12
unnamed: F20.2, J9.13
unnamed: Fb3.2, J9.14
unnamed: Qdb0.3 (D), Rdb0.1
unnamed: Qdb0.1 (G), RN13.1 (R1.1)
unnamed: Qdb1.3 (D), Rdb1.1
unnamed: Qdb1.1 (G), RN13.2 (R2.1)
unnamed: Qdb2.3 (D), Rdb2.1
unnamed: Qdb2.1 (G), RN13.3 (R3.1)
unnamed: Qdb3.3 (D), Rdb3.1
unnamed: Qdb3.1 (G), RN13.4 (R4.1)
unnamed: Qdb4.3 (D), Rdb4.1
unnamed: Qdb4.1 (G), RN12.1 (R1.1)
unnamed: Qdb5.3 (D), Rdb5.1
unnamed: Qdb5.1 (G), RN12.2 (R2.1)
unnamed: Qdb6.3 (D), Rdb6.1
unnamed: Qdb6.1 (G), RN12.3 (R3.1)
unnamed: Qdb7.3 (D), Rdb7.1
unnamed: Qdb7.1 (G), RN12.4 (R4.1)
unnamed: Qdb8.3 (D), Rdb8.1
unnamed: Qdb8.1 (G), RN11.1 (R1.1)
unnamed: Qdb9.3 (D), Rdb9.1
unnamed: Qdb9.1 (G), RN11.2 (R2.1)
unnamed: Qdb10.3 (D), Rdb10.1
unnamed: Qdb10.1 (G), RN11.3 (R3.1)
unnamed: Qdb11.3 (D), Rdb11.1
unnamed: Qdb11.1 (G), RN11.4 (R4.1)
unnamed: C31.1, R17.2, U9.1 (V+)
unnamed: C33.2, U9.35 (VREF1)
unnamed: C34.2, U9.34 (VREF2)
unnamed: C45.1, U11.5 (BST)
unnamed: C46.2, R26.2, R28.2, U11.4 (FB)
unnamed: R21.2, U11.3 (FREQ)
unnamed: C45.2, L3.1, U11.6 (SW)
unnamed: C40.1, U11.2 (VCC)

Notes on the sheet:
30mA*60V=2W
TODO: - temperatures - temperature board using https://www.mouser.it/c/semiconductors/integrated-circuits-ics/power-management-ics/voltage-references/?mounting%20style=SMD%2FSMT&sort=pricing - 0-indexed cells
The cells are 0-indexed. Sn are shifted by one with respect to the LTC numbering. Cn are kept the same indicating then the connection to the negative of cell n.
Short to set VDD as CC12 instead of indipendent supply. For indipendent supply must be VDD>CC12
The NPN transistor should be chosen to have a sufficient Beta over temperature (>40) to supply the necessary supply current.
IREG max = 30mA
TODO: check how much time it takes to read all the 16 channels and then for all the 12 boards send the data to the mainboard alongside the voltages
Fuses 2A >32V

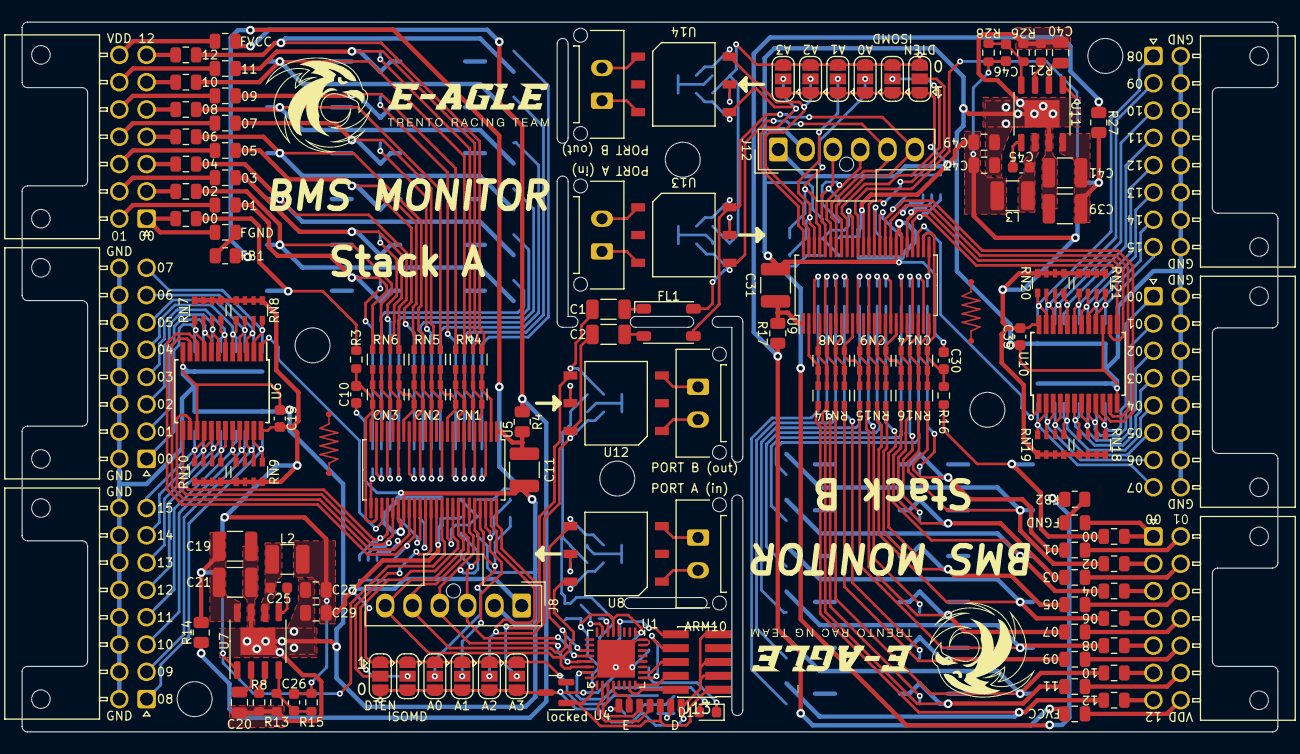
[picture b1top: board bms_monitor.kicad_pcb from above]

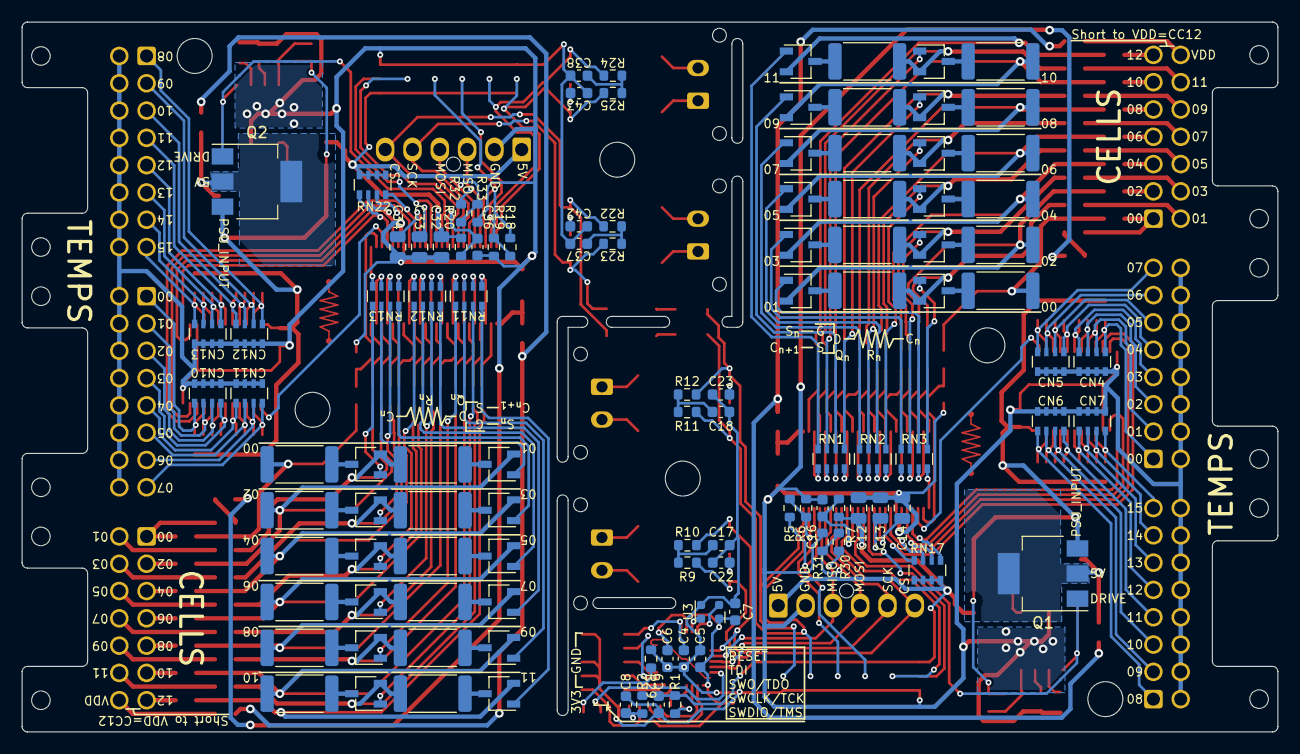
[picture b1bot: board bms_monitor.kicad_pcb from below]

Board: 2 copper layers, 115.0 x 65.0 mm, 244 parts (110 on the bottom side), 277 nets.

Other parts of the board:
locked: MCP1812AT-033-TT; SOT-23

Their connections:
+3.3V: locked.1 (Vout); also elsewhere on the board
+5V: locked.2 (Vin); also elsewhere on the board
GND: locked.3 (GND); also elsewhere on the board

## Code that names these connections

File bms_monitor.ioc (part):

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Mcu.Name=STM32L432K(B-C)Ux
Mcu.Package=UFQFPN32
Mcu.UserName=STM32L432KBUx
PA0.Mode=HSE-External-Clock-Source-for-LittleOrca
PA0.Signal=RCC_CK_IN
PA1.Signal=GPIO_Output
PA10.Mode=IrDA
PA10.Signal=USART1_RX
PA13\ (JTMS-SWDIO).Mode=JTAG_5_pins
PA13\ (JTMS-SWDIO).Signal=SYS_JTMS-SWDIO
PA14\ (JTCK-SWCLK).Mode=JTAG_5_pins
PA14\ (JTCK-SWCLK).Signal=SYS_JTCK-SWCLK
PA15\ (JTDI).Mode=JTAG_5_pins
PA15\ (JTDI).Signal=SYS_JTDI
PA2.Mode=IrDA
PA2.Signal=USART2_TX
PA3.Mode=IrDA
PA3.Signal=USART2_RX
PA4.Signal=GPIO_Output
PA5.Mode=Full_Duplex_Master
PA5.Signal=SPI1_SCK
PA6.Mode=Full_Duplex_Master
PA6.Signal=SPI1_MISO
PA7.Mode=Full_Duplex_Master
PA7.Signal=SPI1_MOSI
PA8.Signal=GPIO_Output
PA9.Mode=IrDA
PA9.Signal=USART1_TX
PB0.Signal=GPIO_Output
PB3\ (JTDO-TRACESWO).Mode=JTAG_5_pins
PB3\ (JTDO-TRACESWO).Signal=SYS_JTDO-SWO
PB4\ (NJTRST).Mode=JTAG_5_pins
PB4\ (NJTRST).Signal=SYS_JTRST
RCC.HSE_VALUE=8000000
board=custom

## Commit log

2022-10-25 First production candidate
2022-10-26 updated readme and license
2022-11-06 updated readme with render
2022-11-06 fixed image
2022-11-08 Removed logo
2022-11-08 removed old document
2022-11-30 deleted old file
2023-02-08 added output schematic pdf
2023-02-16 license change
2023-04-23 Fixed issure #2
2023-04-30 addressed swapped collector emitter of Q1
2023-04-30 changed to bigger footprint for HV caps
2023-05-13 changed SWD connector to smd
2023-05-17 added different VDD pin for external supply
2023-05-19 fixed enable mux
